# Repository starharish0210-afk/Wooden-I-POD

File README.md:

# Wooden I-Pod
# I-pod made of wood

This was a interesting project i had all the freedom i need, but there was something coming up i didnt see i got fever T^T for the whole week and i asked for extension
so i could complete my project on time.

I started from adding items to cart which will make it 10X easier to make the pcb, because we will know the measurement for the components

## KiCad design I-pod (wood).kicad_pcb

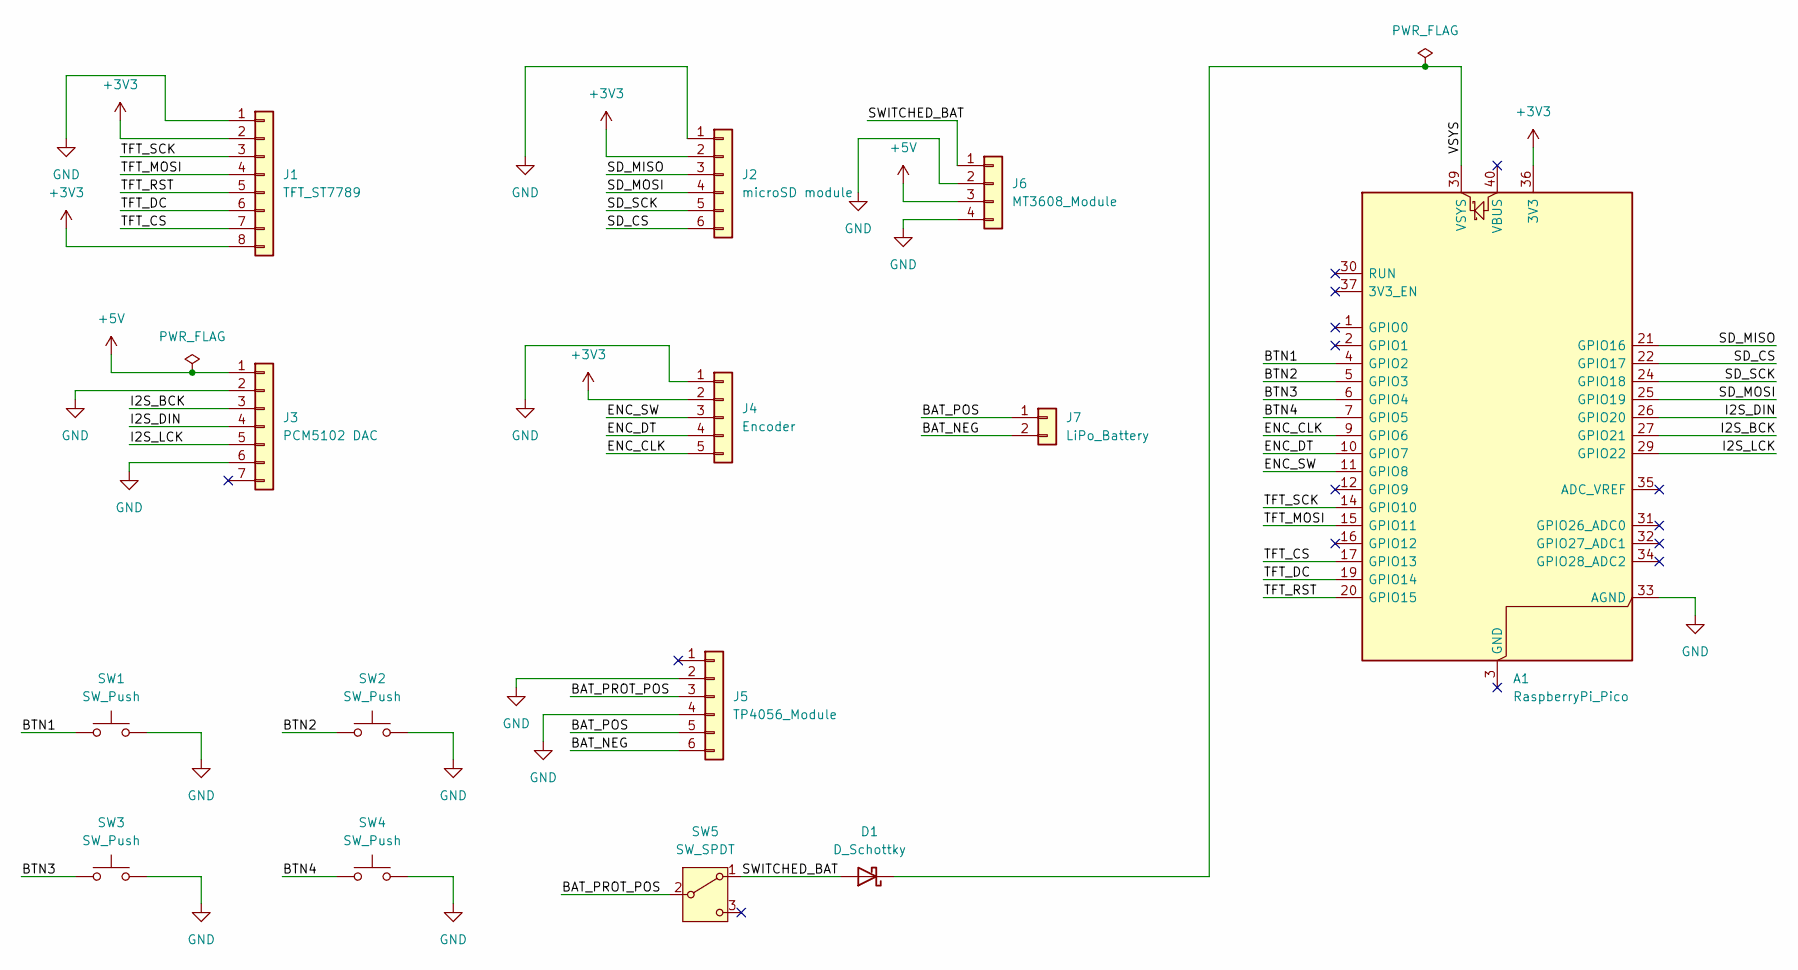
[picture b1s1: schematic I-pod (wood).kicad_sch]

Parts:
A1: RaspberryPi_Pico; RaspberryPi_Pico_Common_Unspecified
D1: D_Schottky; D_DO-41_SOD81_P7.62mm_Horizontal
J1: TFT_ST7789; PinHeader_1x08_P2.54mm_Vertical
J2: microSD module; PinHeader_1x06_P2.54mm_Vertical
J3: PCM5102 DAC; PinHeader_1x06_P2.54mm_Vertical
J4: Encoder; PinHeader_1x05_P2.54mm_Vertical
J5: TP4056_Module; PinHeader_1x06_P2.54mm_Vertical
J6: MT3608_Module; PinHeader_1x04_P2.54mm_Vertical
J7: LiPo_Battery; PinHeader_1x02_P2.54mm_Vertical
SW1, SW2, SW3, SW4: SW_Push; SW_PUSH_6mm
SW5: SW_SPDT; PinHeader_1x03_P2.54mm_Vertical

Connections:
+3V3: A1.36 (3V3), J1.2, J1.8, J2.2, J4.2
+5V: J3.1, J6.3
/BAT_NEG: J5.6, J7.2
/BAT_POS: J5.5, J7.1
/BAT_PROT_POS: J5.3, SW5.2 (B)
/BTN1: A1.4 (GPIO2), SW1.1
/BTN2: A1.5 (GPIO3), SW2.1
/BTN3: A1.6 (GPIO4), SW3.1
/BTN4: A1.7 (GPIO5), SW4.1
/ENC_CLK: A1.9 (GPIO6), J4.5
/ENC_DT: A1.10 (GPIO7), J4.4
/ENC_SW: A1.11 (GPIO8), J4.3
/I2S_BCK: A1.27 (GPIO21), J3.3
/I2S_DIN: A1.26 (GPIO20), J3.4
/I2S_LCK: A1.29 (GPIO22), J3.5
/SD_CS: A1.22 (GPIO17), J2.6
/SD_MISO: A1.21 (GPIO16), J2.3
/SD_MOSI: A1.25 (GPIO19), J2.4
/SD_SCK: A1.24 (GPIO18), J2.5
/SWITCHED_BAT: D1.2 (A), J6.1, SW5.1 (A)
/TFT_CS: A1.17 (GPIO13), J1.7
/TFT_DC: A1.19 (GPIO14), J1.6
/TFT_MOSI: A1.15 (GPIO11), J1.4
/TFT_RST: A1.20 (GPIO15), J1.5
/TFT_SCK: A1.14 (GPIO10), J1.3
/VSYS: A1.39 (VSYS), D1.1 (K)
GND: A1.33 (AGND), J1.1, J2.1, J3.2, J3.6, J4.1, J5.2, J5.4, J6.2, J6.4, SW1.2, SW2.2, SW3.2, SW4.2

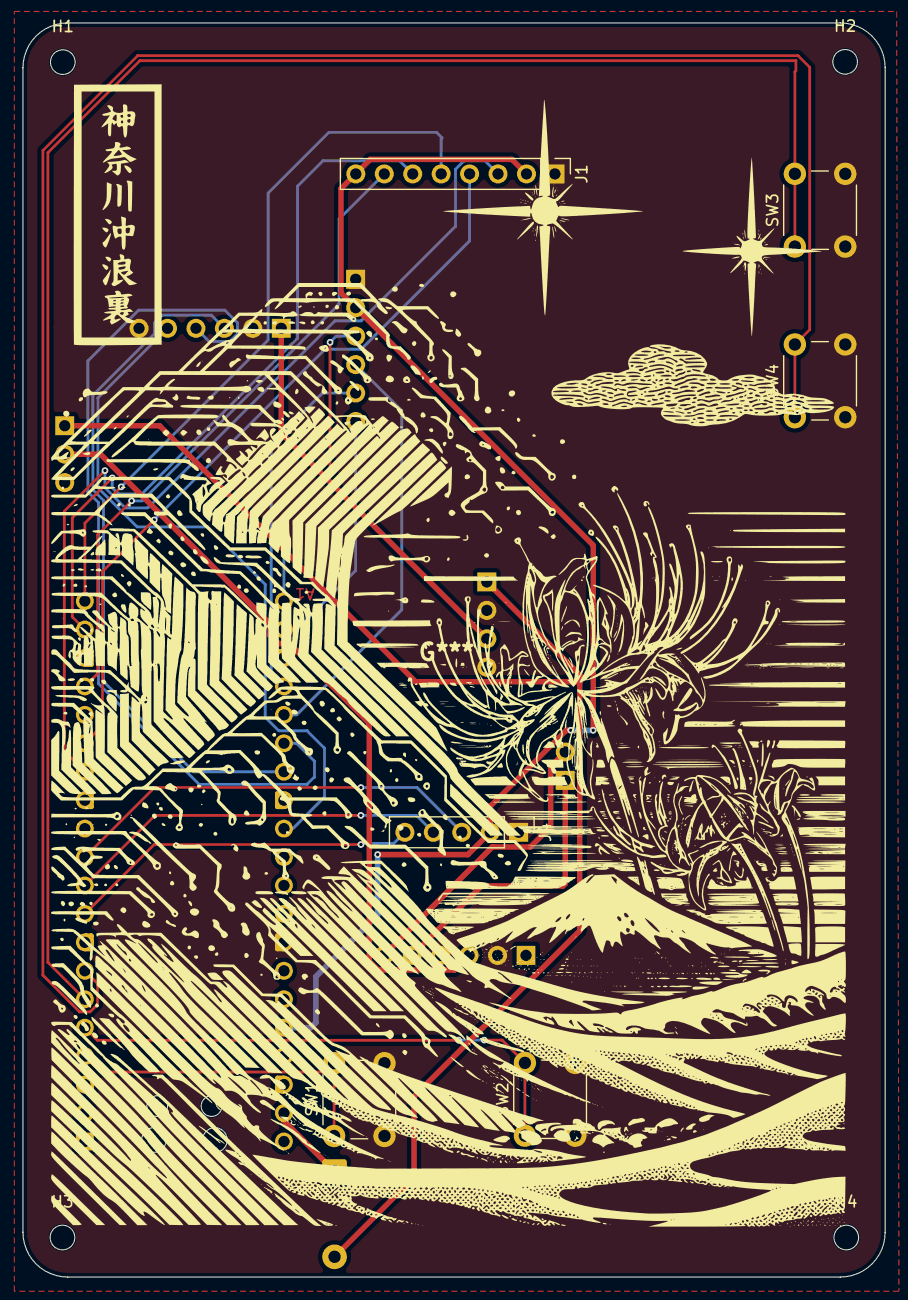
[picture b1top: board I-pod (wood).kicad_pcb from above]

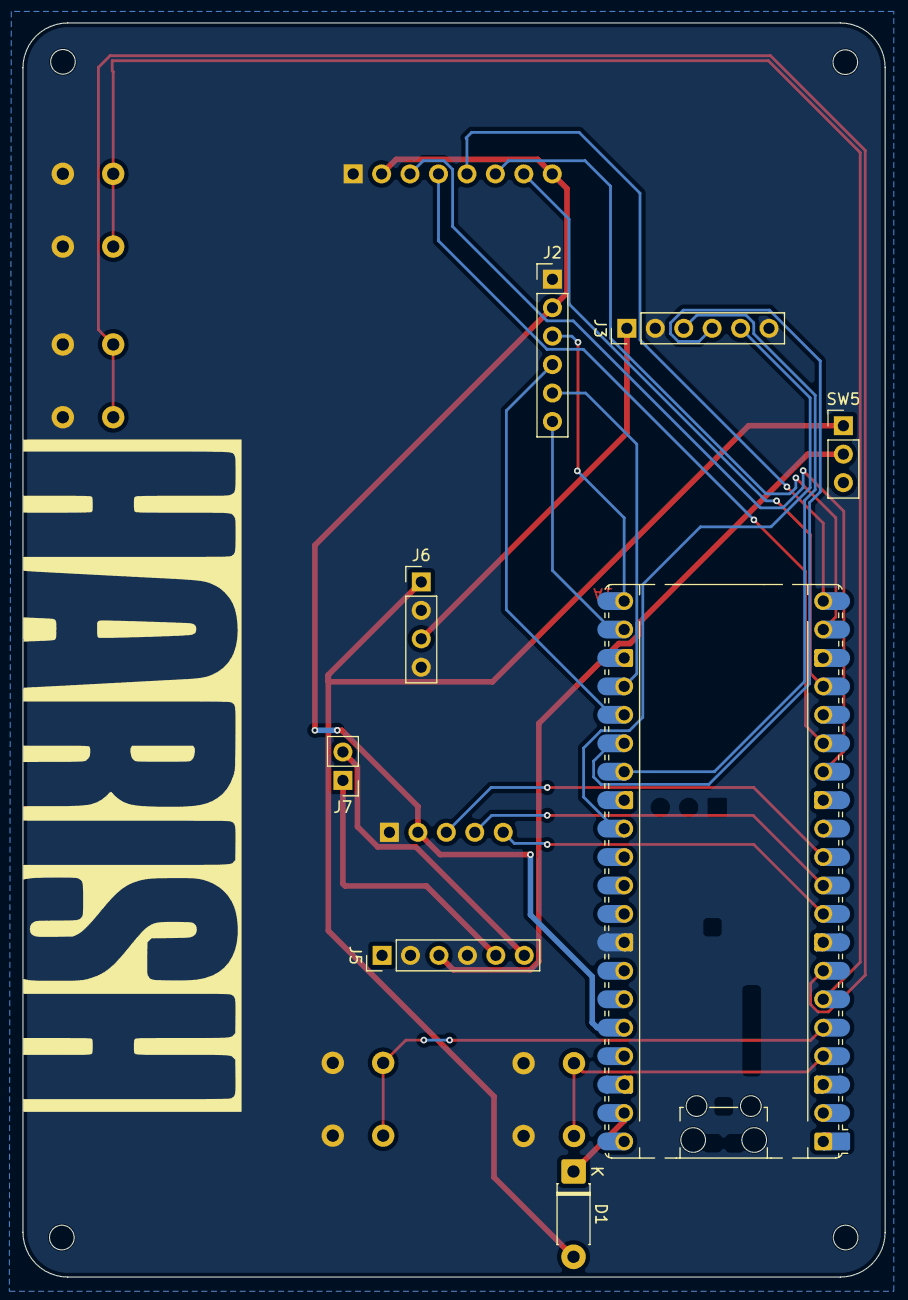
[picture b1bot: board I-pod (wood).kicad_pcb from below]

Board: 2 copper layers, 77.0 x 112.0 mm, 18 parts (8 on the bottom side), 27 nets.

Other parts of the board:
H1: MountingHole 1; MountingHole_2.2mm_M2
H2: MountingHole 2; MountingHole_2.2mm_M2
H3: MountingHole 3; MountingHole_2.2mm_M2
H4: MountingHole 4; MountingHole_2.2mm_M2

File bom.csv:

Designator,Footprint,Quantity,Value,LCSC Part #
A1,RaspberryPi_Pico_Common_Unspecified,1,RaspberryPi_Pico,
D1,D_DO-41_SOD81_P7.62mm_Horizontal,1,D_Schottky,
J1,PinHeader_1x08_P2.54mm_Vertical,1,TFT_ST7789,
J2,PinHeader_1x06_P2.54mm_Vertical,1,microSD module,
J3,PinHeader_1x06_P2.54mm_Vertical,1,PCM5102 DAC,
J4,PinHeader_1x05_P2.54mm_Vertical,1,Encoder,
J5,PinHeader_1x06_P2.54mm_Vertical,1,TP4056_Module,
J6,PinHeader_1x04_P2.54mm_Vertical,1,MT3608_Module,
J7,PinHeader_1x02_P2.54mm_Vertical,1,LiPo_Battery,
"SW1, SW2, SW3, SW4",SW_PUSH_6mm,4,SW_Push,
SW5,PinHeader_1x03_P2.54mm_Vertical,1,SW_SPDT,

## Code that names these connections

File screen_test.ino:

// Wooden iPod - step 1: screen test (Arduino-Pico core)
// Starter written with AI help; the rest of the firmware is written by me.
#include <Adafruit_GFX.h>
#include <Adafruit_ST7789.h>
#include <SPI.h>

#define TFT_CS   13
#define TFT_DC   14
#define TFT_RST  15

Adafruit_ST7789 tft(&SPI1, TFT_CS, TFT_DC, TFT_RST);

void setup() {
  Serial.begin(115200);

  SPI1.setSCK(10);   // screen clock
  SPI1.setTX(11);    // screen data (MOSI)

  tft.init(240, 240);
  tft.setRotation(2);          // try 0, 1, 2 or 3 if the picture is the wrong way up
  tft.fillScreen(ST77XX_BLACK);

  tft.setTextColor(ST77XX_WHITE);
  tft.setTextSize(3);
  tft.setCursor(10, 40);
  tft.println("Wooden iPod");
  tft.setTextSize(2);
  tft.setCursor(10, 90);
  tft.println("screen works");
}

void loop() {
}
